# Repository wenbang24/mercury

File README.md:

# mercury — KiCad keyboard PCB

Clone with submodules:

```sh
git clone --recursive https://github.com/wenbang24/mercury.git
```

Open `mercury.kicad_pro` in KiCad 9. The schematic describes one keyboard half.

## Libraries

[marbastlib](https://github.com/ebastler/marbastlib) (CERN-OHL-P v2) is a
submodule pinned to **2025.08.03** (`b628d38`), the last KiCad 9 compatible
release. Do not update to master: it uses KiCad 10 format.
Project-level library tables register all bundled symbol and footprint libraries
using `${KIPRJMOD}` paths. Stock KiCad libraries remain available through the
global tables for other standard parts.

- XIAO nRF52840 **Plus**: official Seeed footprint
  `mercury:XIAO-nRF52840-Plus-SMD_SilkFix` in `mercury.pretty`,
  and symbol `mercury:XIAO-nRF52840_Plus_SMD` in `mercury.kicad_sym`.
  Source: [Seeed Studio OPL](https://github.com/Seeed-Studio/OPL_Kicad_Library/tree/3be8215d3db652e2f62269913cb1fddd5e737d38/Seeed%20Studio%20XIAO%20Series%20Library),
  revision `3be8215d3db652e2f62269913cb1fddd5e737d38` (KiCad 9).
  Copyright/attribution: Seeed Studio and OPL contributors, **CC BY-SA 4.0**;
  see [retained licence](SEEED-LICENSE.txt). The footprint derivative removes
  only two F.SilkS side-outline lines overlapping the castellated lands and
  two USB corner arcs crossing the flush board edge. Copper, paste, mask,
  courtyards and all other geometry are unchanged. Symbol changes: battery pin numbers
  32/33 corrected to **28/29**, pin 26 named **RST**, and the footprint property
  points to the project library. The schematic adds MPN `102010672`, manufacturer
  Seeed Studio and LCSC **C48405120** for JLCPCB's bare-module SMD assembly.
- PG1316S switch footprint: `marbastlib-xp-choc:SW_PG1316S`
  (`libs/marbastlib/footprints/marbastlib-xp-choc.pretty`).
- Common keyboard footprints in `marbastlib-various`:
  - Reset pushbutton: `marbastlib-various:SW_SPST_SKQG_WithStem`.
  - Power slide switch: `marbastlib-various:SW_MSK12C02-HB`.
  - JST ACH two-pin battery connector: `marbastlib-various:CON_JST_ACH_BM02B`.

The bundled 3D model references use `${KICAD8_3RD_PARTY}` and only resolve
if marbastlib is also installed through KiCad's Plugin and Content Manager.
The git submodule alone provides symbols and footprints, not resolved 3D models.

## Keyboard schematic

One half has 18 keys: three rows of five and three thumb keys. Both halves use
the same electrical design, with separate mirrored PCBs. Switches SW1–SW15 run
row-major from outer/pinky to inner/index; SW16–SW18 are the thumbs.
Each switch connects one dedicated GPIO to GND; **there are no diodes**.

| Switch | XIAO GPIO | nRF52840 GPIO | U1 pad |
| --- | --- | --- | --- |
| SW1 | D0 | P0.02 | 1 |
| SW2 | D1 | P0.03 | 2 |
| SW3 | D2 | P0.28 | 3 |
| SW4 | D3 | P0.29 | 4 |
| SW5 | D4 | P0.04 | 5 |
| SW6 | D5 | P0.05 | 6 |
| SW7 | D6 | P1.11 | 7 |
| SW8 | D7 | P1.12 | 8 |
| SW9 | D8 | P1.13 | 9 |
| SW10 | D9 | P1.14 | 10 |
| SW11 | D10 | P1.15 | 11 |
| SW12 | D11 | P0.15 | 15 |
| SW13 | D12 | P0.19 | 16 |
| SW14 | D13 | P1.01 | 17 |
| SW15 | D14 / NFC1 | P0.09 | 18 |
| SW16 | D17 | P1.03 | 21 |
| SW17 | D18 | P1.05 | 22 |
| SW18 | D19 | P1.07 | 23 |

ZMK requires **direct kscan**, pull-ups and active-low inputs, not a matrix
scanner. Configure `&uicr { nfct-pins-as-gpios; };` to use NFC1 as GPIO;
this disables NFC. D15/P0.10 and D16/P0.31 are not key inputs. D16 remains
reserved for the module's battery divider: its edge label BAT is **not BAT+**.
Unused D15, D16, 3V3, VBUS, SWDIO and SWCLK have no-connect flags.
All three GND pads (13, 27 and 29) connect to GND.

J1 pin 1 is battery positive, through SW19 common pin 2 to throw pin 1,
then U1 BAT+ (28). J1 pin 2 connects to BAT- (29) and GND.
SW19 throw pin 3 is unused. SW20 connects RST (26) to GND.
Power flags on switched battery positive and GND supply ERC's power-input checks.
SW19 disconnects the battery, including its charging path: charge with the switch
on. USB can still power the keyboard with the battery switch off. Use a suitable
protected single-cell Li-ion/LiPo battery; the XIAO contains its charger.

## PCBs

`mercury.kicad_pcb` is the routed right half, with all 22 components on F.Cu.
`mercury-left.kicad_pcb` has mirrored placement and outline, but its footprints
are not mirrored: all 22 components remain on F.Cu, with readable front
silkscreen. U1's USB points up on both halves; SW19's actuator faces the
respective board edge. Both boards have components on one face only;
traces and vias may use both copper layers.
Signal tracks are 0.25 mm; BAT and GND tracks are 0.4 mm. There is no ground pour.

### Layout geometry

Placement and contour are adapted from [Chocofi by pashutk](https://github.com/pashutk/chocofi),
source revision `273676d11b06785fb5a1a94860a39fc36c38baba`, licensed under the
**CERN Open Hardware Licence v2 – Permissive (CERN-OHL-P)**; see
[the retained licence](CHOCOfi-LICENSE.txt). Only geometry is copied: Mercury's
schematic, electronics, footprints and routing are independent of Chocofi.
Modified 2026-11-07: reflected the source half for the right hand, scaled X by
17/18 (Y unchanged), refitted circular outline fillets and extended the contour
locally for XIAO/power parts. No source mounting holes are copied.

PG1316S pitch is **17 × 17 mm**, versus Chocofi's 18 × 17 mm. From outer/pinky
COL0 to inner/index COL4, top-row Y stagger is **0, −12, −18, −11.38, −9 mm**.
Finger rows are 17 mm apart (the source's COL3 bottom row retains its 0.005 mm
offset). On the right, column X positions are **137, 120, 103, 86, 69 mm**,
and SW1 is anchored at **(137, 45) mm**. Thumb placements/rotations are:

| Switch | Position X, Y (mm) | Rotation | Thumb |
| --- | --- | --- | --- |
| SW16 | 91.5722, 87.59 | −180° | Outer, COL2 |
| SW17 | 72.6361, 90.18 | −165° | Middle, COL3 |
| SW18 | 53.1806, 93.39 | 120° | Inner, COL4 |

The former diode-cluster area remains empty. Run
`/usr/bin/python3 scripts/check_layout.py` to verify direct GPIO assignments,
unchanged switch/U1-centre placement, mirrored left placement, widths,
footprint/keycap containment, USB overhang and antenna/underside-pad keepouts.
The stepped column and thumb edges are straight between rounded corners, with
the small Chocofi-derived perimeter tabs removed. U1 is at
**(49.54, 40.39) mm, +90°**, USB pointing up and nominally flush with the local
controller-wing edge (0.08 mm tip overhang). A rounded diagonal transition
to the column edge preserves keycap coverage without tabs. J1 (49.54, 73.4), reset SW20 (50.5, 79.6) and power
SW19 (43.3, 83.5; 90°) occupy the lower controller wing; SW19's actuator faces its outer
edge. The left board mirrors these positions without mirroring the footprints.

Regenerate left placement after right-board edits: `/usr/bin/python3 scripts/make_left.py`.
**This discards all left routing.** Nets and pad assignments are retained from
the right board; footprint X coordinates are reflected about the outline's
vertical centre and rotations are negated without flipping the footprints,
except U1 which remains +90° so USB points up. Its rule areas translate with
the unmirrored controller rather than mirroring the underside pad pattern.

### Antenna and underside-pad keepouts

Both copper layers have a **13.6 × 2.5 mm** antenna rule area: relative to U1's
centre with USB up, X **−6.8..+6.8 mm**, Y **+7.9..+10.4 mm**. This forbids
tracks, vias, pads and copper pours in the central non-castellated tail at the
end opposite USB. It is derived from ANT1 (`ANTENNA-AN3216`) and the tail outline
in [Seeed's Plus v1.1 hardware project](https://files.seeedstudio.com/wiki/XIAO-BLE/Seeed_Studio_XIAO_nRF52840_Plus.zip),
not a published guaranteed RF clearance specification. Keep batteries/metal
away from this region; RF performance still requires physical testing.
Each exposed underside pad (24–29) also has a both-layer **via-only keepout**,
covering its land's bounding rectangle plus 0.2 mm on every side. Matching
official host lands and paste apertures remain present for reflow assembly.
The DSN exporter retains these rule areas as copper/via keepouts.

### Checks

```sh
kicad-cli sch erc --severity-all mercury.kicad_sch
kicad-cli pcb drc --severity-all --schematic-parity mercury.kicad_pcb
kicad-cli pcb drc --severity-all mercury-left.kicad_pcb
/usr/bin/python3 scripts/check_layout.py
mkdir -p fab
kicad-cli sch export netlist --format kicadxml --output fab/direct.xml mercury.kicad_sch
/usr/bin/python3 scripts/check_netlist.py fab/direct.xml
/usr/bin/python3 scripts/test_layout.py
/usr/bin/python3 scripts/check_xiao_footprint.py /home/ubuntu/analysis/xiao-plus/OPL_Kicad_Library
```

The last check reads the official footprint directly from commit `3be8215` in
the supplied OPL clone (its checkout branch does not matter). It asserts exact
equality of all 29 pads, including copper/paste/mask layers and attributes,
and all other non-silkscreen geometry. Only the four removed F.SilkS graphics
and the footprint identifier may differ. The unused unmodified copy is not
included in this project.

From the repository root, regenerate and route using the installed Temurin
JDK 25 and official Freerouting 2.5.0 release jar:

```sh
/usr/bin/python3 scripts/make_left.py
cp mercury.kicad_pro mercury-left.kicad_pro
mkdir -p fab/left-routing
/usr/bin/python3 scripts/route_board.py export mercury-left.kicad_pcb fab/left-routing/left.dsn
/home/ubuntu/tools/freerouting/jdk-25.0.5+8/bin/java -Djava.awt.headless=true \
  -jar /home/ubuntu/tools/freerouting/freerouting-2.5.0.jar \
  -de fab/left-routing/left.dsn -do fab/left-routing/left.ses \
  --gui.enabled=false -da --router.autorouter.max_passes=50 --router.optimizer.max_threads=1
/usr/bin/python3 scripts/route_board.py import mercury-left.kicad_pcb fab/left-routing/left.ses
kicad-cli pcb drc --severity-all mercury-left.kicad_pcb
```

To route an unrouted right board, use the same export / Java / import commands
with `mercury.kicad_pcb` and right-specific DSN/SES filenames, then run
`kicad-cli pcb drc --severity-all --schematic-parity mercury.kicad_pcb`.
SES import does not rip up existing copper: remove existing tracks/vias before
exporting when replacing a route.

The ignored local `mercury-left.kicad_pro` copy supplies identical net classes
and DRC settings. The export adds 0.55 mm edge keepouts to the DSN only; it
supports straight and circular-arc edges (arcs are sampled every ≤0.1 mm for
DSN keepouts; the board retains true arcs). Import enforces the track
widths above, including any Freerouting neckdowns. Always check DRC after
import: edits to placement may require manual escape/clearance repairs before
the board is fabrication-ready. No DRC rules are relaxed by these scripts.

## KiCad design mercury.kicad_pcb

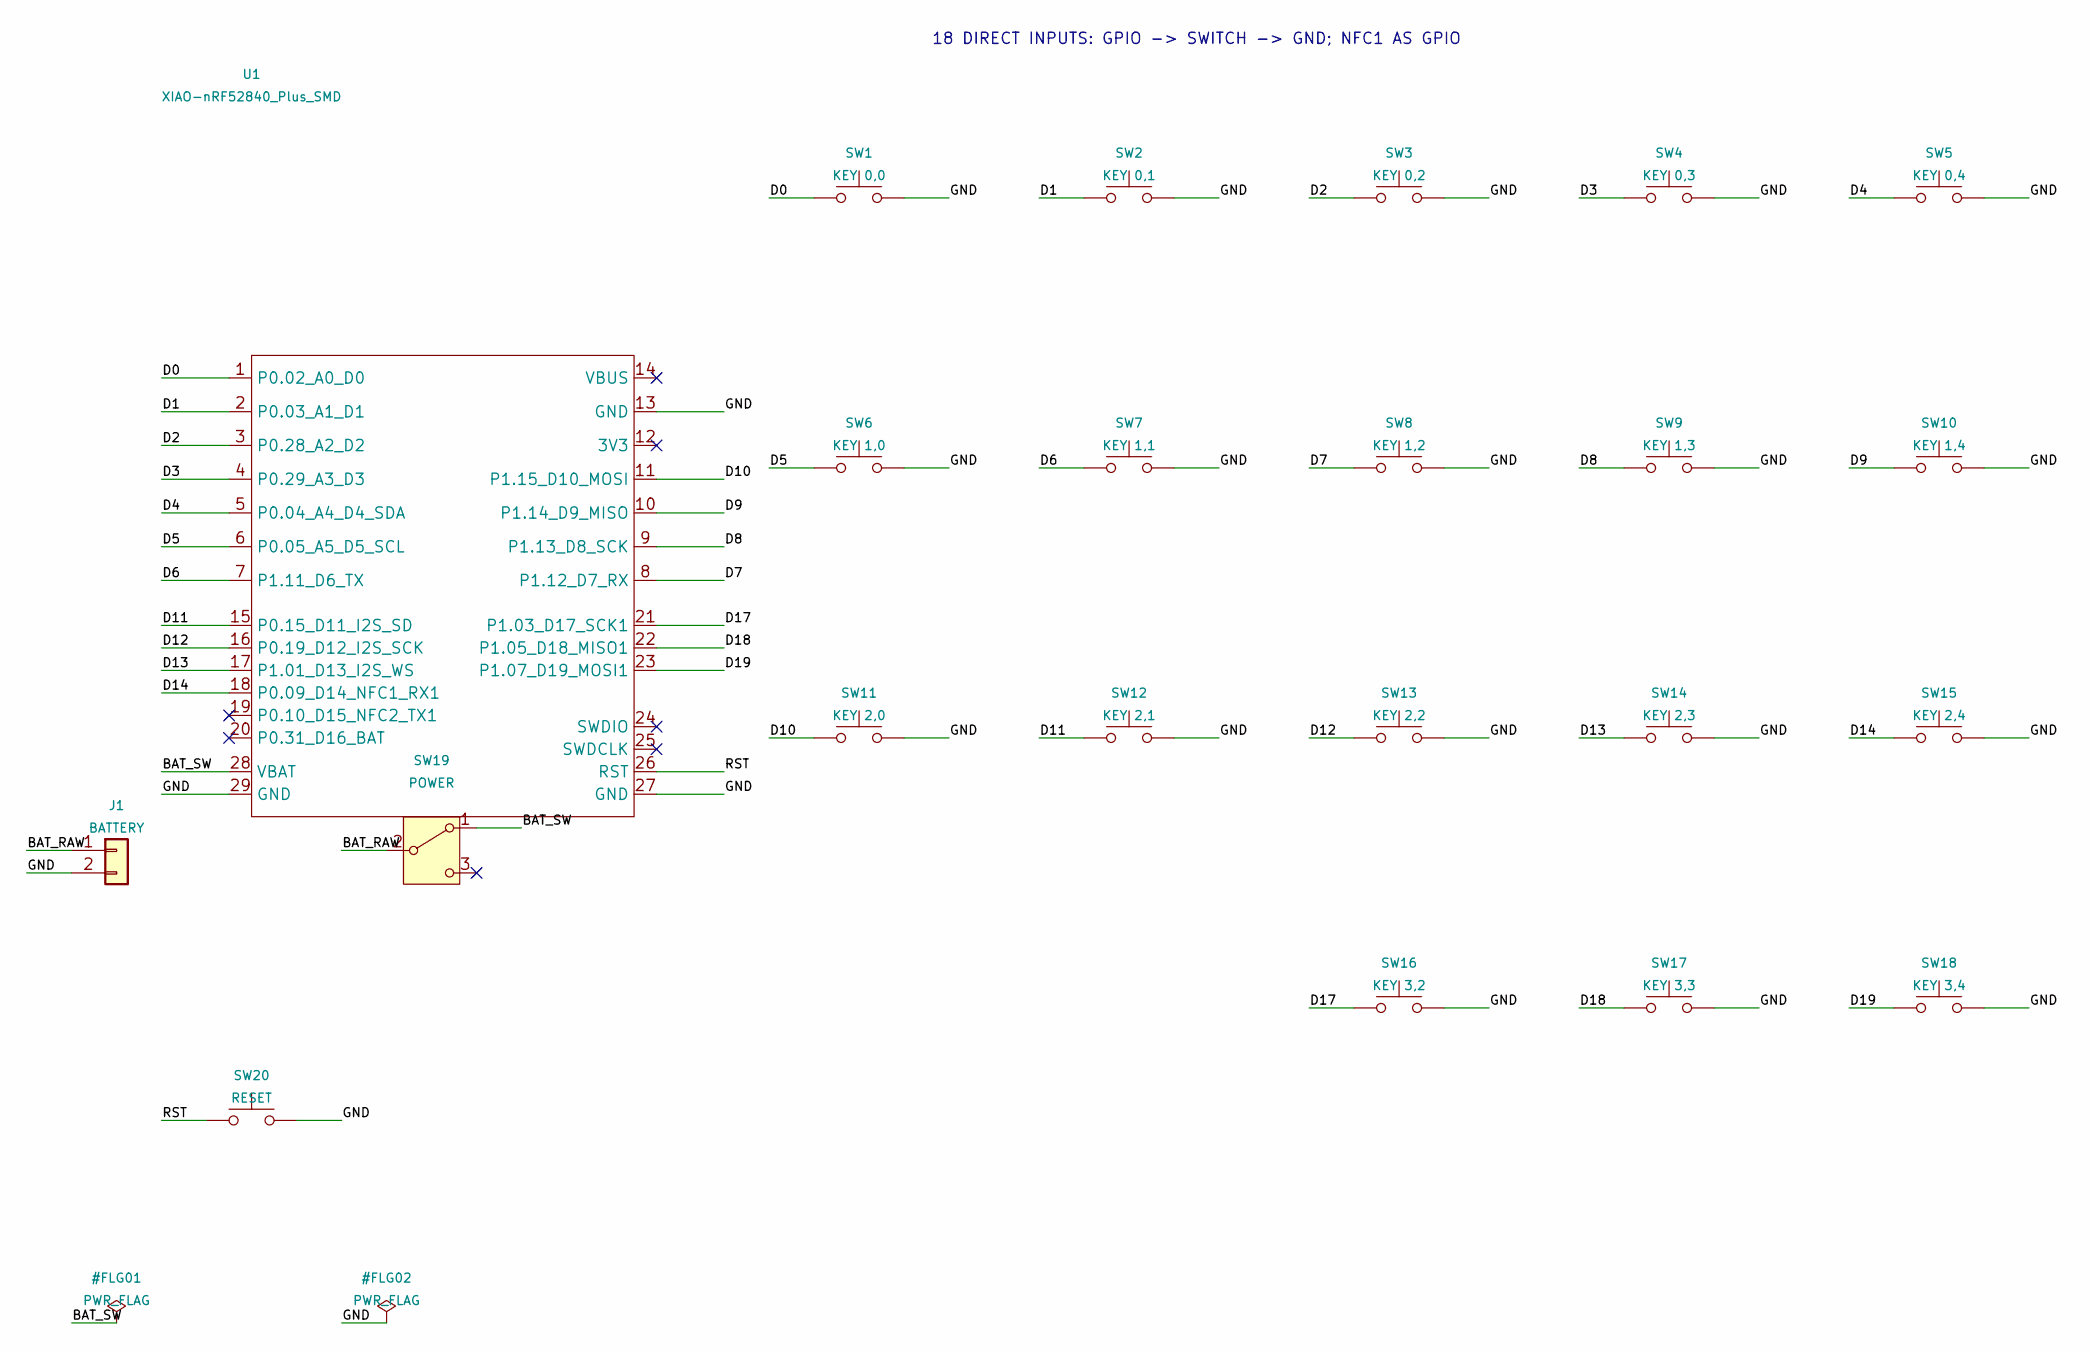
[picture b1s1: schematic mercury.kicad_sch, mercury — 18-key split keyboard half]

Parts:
J1: BATTERY; CON_JST_ACH_BM02B
SW1: KEY 0,0; SW_PG1316S
SW2: KEY 0,1; SW_PG1316S
SW3: KEY 0,2; SW_PG1316S
SW4: KEY 0,3; SW_PG1316S
SW5: KEY 0,4; SW_PG1316S
SW6: KEY 1,0; SW_PG1316S
SW7: KEY 1,1; SW_PG1316S
SW8: KEY 1,2; SW_PG1316S
SW9: KEY 1,3; SW_PG1316S
SW10: KEY 1,4; SW_PG1316S
SW11: KEY 2,0; SW_PG1316S
SW12: KEY 2,1; SW_PG1316S
SW13: KEY 2,2; SW_PG1316S
SW14: KEY 2,3; SW_PG1316S
SW15: KEY 2,4; SW_PG1316S
SW16: KEY 3,2; SW_PG1316S
SW17: KEY 3,3; SW_PG1316S
SW18: KEY 3,4; SW_PG1316S
SW19: POWER; SW_MSK12C02-HB
SW20: RESET; SW_SPST_SKQG_WithStem
U1: XIAO-nRF52840_Plus_SMD; XIAO-nRF52840-Plus-SMD_SilkFix; MPN 102010672; LCSC C48405120

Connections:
/BAT_RAW: J1.1, SW19.2 (B)
/BAT_SW: SW19.1 (A), U1.28 (VBAT)
/D0: SW1.1, U1.1 (P0.02_A0_D0)
/D1: SW2.1, U1.2 (P0.03_A1_D1)
/D2: SW3.1, U1.3 (P0.28_A2_D2)
/D3: SW4.1, U1.4 (P0.29_A3_D3)
/D4: SW5.1, U1.5 (P0.04_A4_D4_SDA)
/D5: SW6.1, U1.6 (P0.05_A5_D5_SCL)
/D6: SW7.1, U1.7 (P1.11_D6_TX)
/D7: SW8.1, U1.8 (P1.12_D7_RX)
/D8: SW9.1, U1.9 (P1.13_D8_SCK)
/D9: SW10.1, U1.10 (P1.14_D9_MISO)
/D10: SW11.1, U1.11 (P1.15_D10_MOSI)
/D11: SW12.1, U1.15 (P0.15_D11_I2S_SD)
/D12: SW13.1, U1.16 (P0.19_D12_I2S_SCK)
/D13: SW14.1, U1.17 (P1.01_D13_I2S_WS)
/D14: SW15.1, U1.18 (P0.09_D14_NFC1_RX1)
/D17: SW16.1, U1.21 (P1.03_D17_SCK1)
/D18: SW17.1, U1.22 (P1.05_D18_MISO1)
/D19: SW18.1, U1.23 (P1.07_D19_MOSI1)
/GND: J1.2, SW1.2, SW2.2, SW3.2, SW4.2, SW5.2, SW6.2, SW7.2, SW8.2, SW9.2, SW10.2, SW11.2, SW12.2, SW13.2, SW14.2, SW15.2, SW16.2, SW17.2, SW18.2, SW20.2, U1.13 (GND), U1.27 (GND), U1.29 (GND)
/RST: SW20.1, U1.26 (RST)

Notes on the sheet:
18 DIRECT INPUTS: GPIO -> SWITCH -> GND; NFC1 AS GPIO

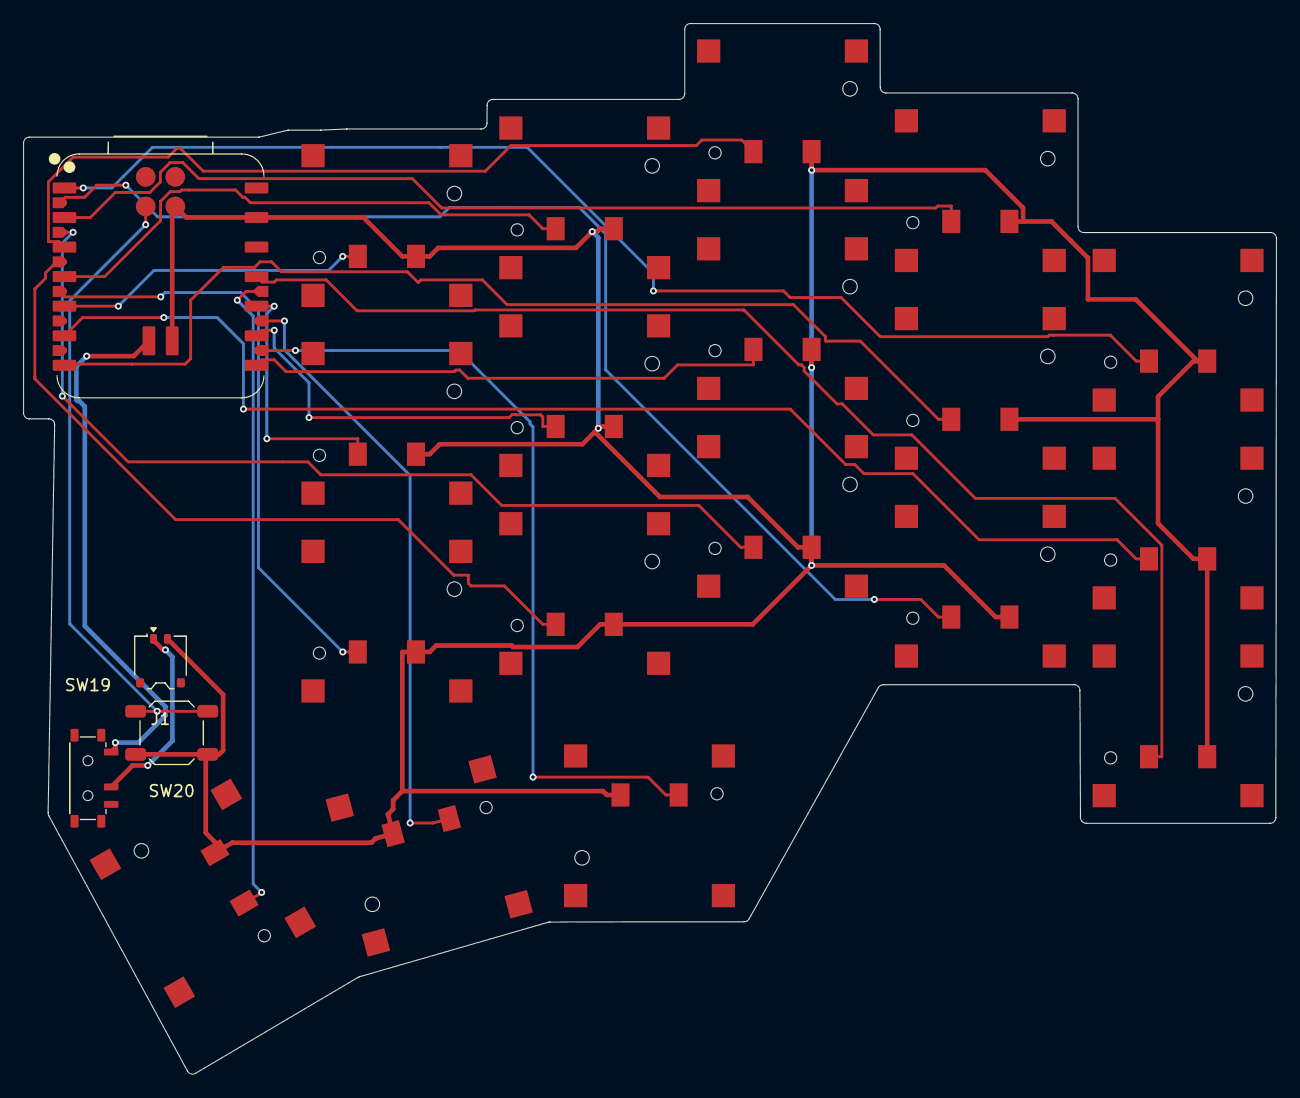
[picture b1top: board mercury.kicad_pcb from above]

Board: 2 copper layers, 107.7 x 90.3 mm, 22 parts (0 on the bottom side), 22 nets.
